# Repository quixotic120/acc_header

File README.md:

# acc_header

a small PCB with molex plugs for 12v and 5v accessories. Simple and not of much use outside of my purpose but who knows!

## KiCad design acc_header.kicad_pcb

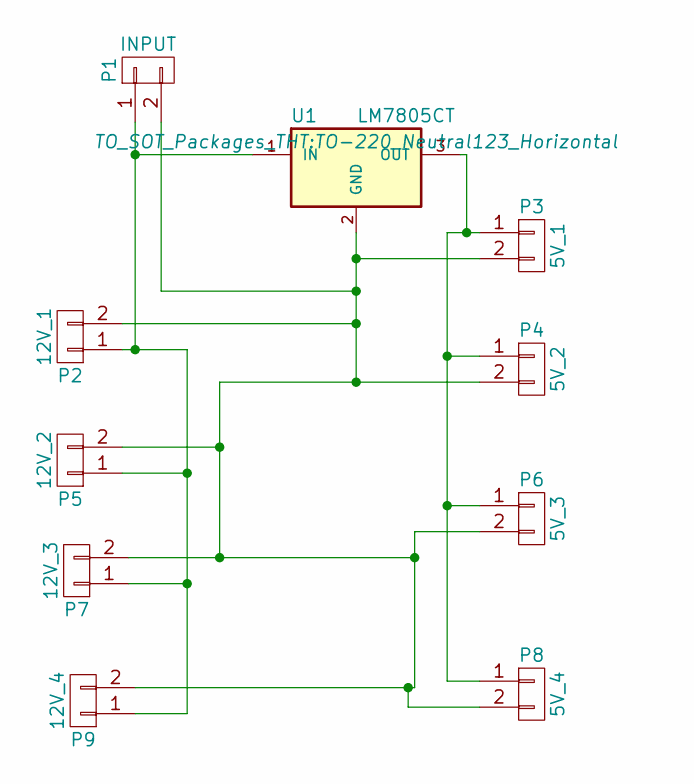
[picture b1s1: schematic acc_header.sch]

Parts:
P1: INPUT; AB2_TB_02_RA_5.08MM_L-GRN
P2: 12V_1; CONN_KK_2.54_2W
P3: 5V_1; CONN_KK_2.54_2W
P4: 5V_2; CONN_KK_2.54_2W
P5: 12V_2; CONN_KK_2.54_2W
P6: 5V_3; CONN_KK_2.54_2W
P7: 12V_3; CONN_KK_2.54_2W
P8: 5V_4; CONN_KK_2.54_2W
P9: 12V_4; CONN_KK_2.54_2W
U1: LM7805CT; TO-220_Neutral123_Horizontal

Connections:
unnamed: P1.1, P2.1, P5.1, P7.1, P9.1, U1.1 (IN)
unnamed: P1.2, P2.2, P3.2, P4.2, P5.2, P6.2, P7.2, P8.2, P9.2, U1.2 (GND)
unnamed: P3.1, P4.1, P6.1, P8.1, U1.3 (OUT)

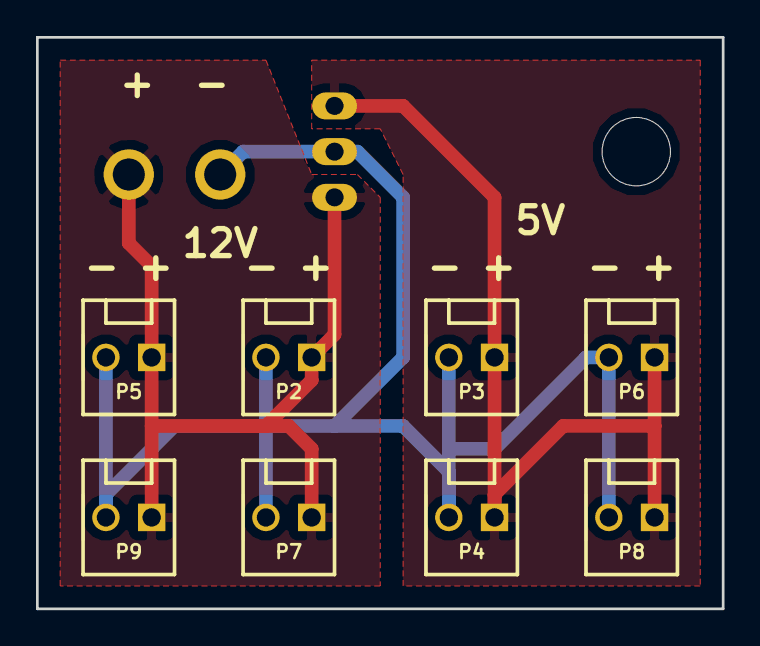
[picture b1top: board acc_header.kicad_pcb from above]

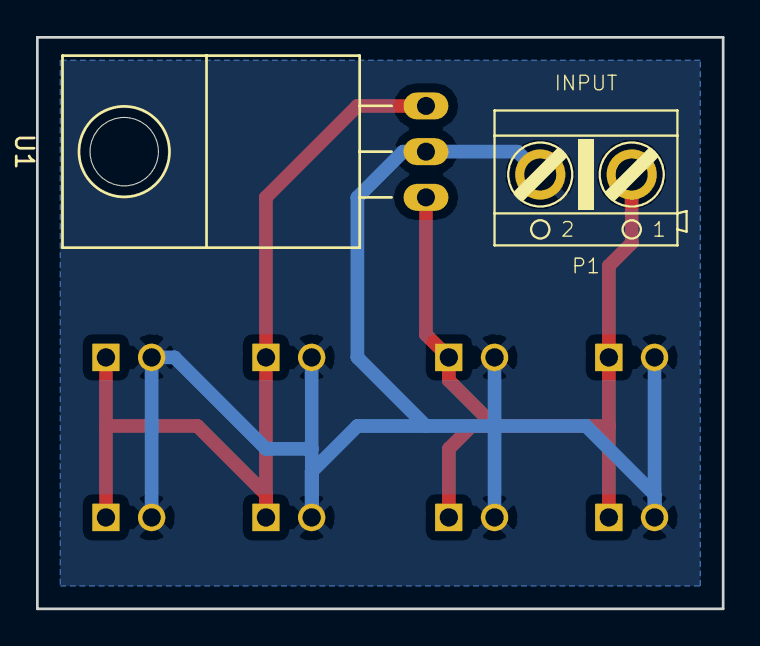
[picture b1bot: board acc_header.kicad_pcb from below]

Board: 2 copper layers, 38.1 x 31.7 mm, 10 parts (2 on the bottom side), 3 nets.

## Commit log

2016-07-09 accessory header
    simple 12v and 5v header for accessories. Uses murata dc-dc converter
    but 7805 would also work
